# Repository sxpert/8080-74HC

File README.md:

8080 processor made of 74HC chips

original from http://userweb.alles.or.jp/chunichidenko/index.htm

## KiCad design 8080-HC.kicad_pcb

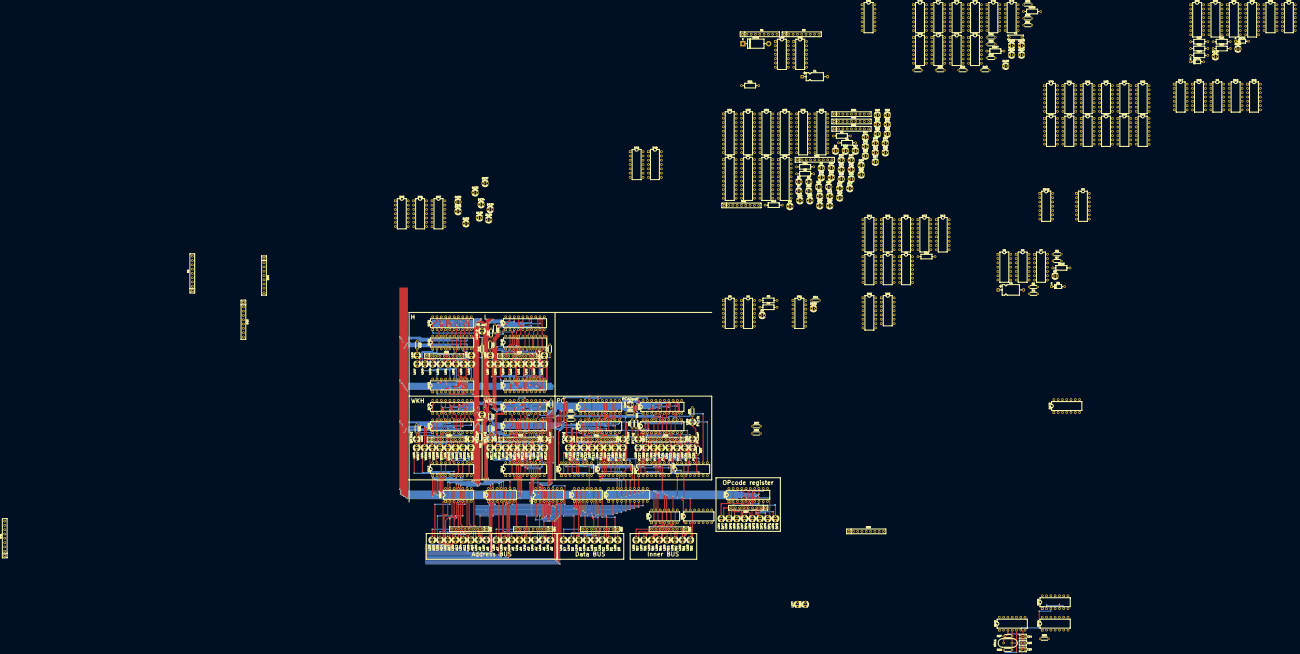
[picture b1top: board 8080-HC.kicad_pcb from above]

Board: 4 copper layers, 360 parts (0 on the bottom side), 494 nets.

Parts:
B1, B3, B5, B41, B43, B44: 1K; R_Array_SIP9
B25, B26, B29, B30, B31, B32, B33, B34, B35, B36, B37: 2.2K; R_Array_SIP9
B38: 22K; R_Array_SIP9
C1: CP; CP_Axial_L10.0mm_D4.5mm_P15.00mm_Horizontal
C2: C; C_Rect_L9.0mm_W2.5mm_P7.50mm_MKT
C4: 2.2uF; CP_Axial_L10.0mm_D6.0mm_P15.00mm_Horizontal
C14, C15: 22pF; C_Rect_L4.0mm_W2.5mm_P2.50mm
C16: 56pF; C_Rect_L4.0mm_W2.5mm_P2.50mm
D1, D2, D3, D5, D6, D7, D8, D9, D10, D11, D12, D13, D14, D15, D16, D17, D18, D19, D20, D21, D22, D23, D24, D25, D26, D27, D28, D29, D30, D31, D32, D33, D34, D35, D36, D37, D38, D39, D40, D41, D42, D43, D44, D45, D46, D47, D48, D129, D130, D132, D133, D134, D135, D136, D137, D138, D139, D140, D147, D148, D149, D150, D151, D152: LED_Small_ALT; LED_D3.0mm
D4, D141, D142: 1N4148; D_DO-35_SOD27_P7.62mm_Horizontal
D131: 1N5400; D_DO-201AD_P15.24mm_Horizontal
L145-2, L146, L155, L156, L164-2, L210, L211, L212, L213, L214, L215, L216, L217, L220, L221, L222, L223, L224, L225, L226, L227, L277, L278: LED; LED_D3.0mm
L147, L148, L149, L150, L151, L152, L153, L154, L157, L158, L159, L160, L161, L162, L163, L164, L187, L188, L189, L190, L191, L192, L193, L194, L195, L196, L197, L198, L199, L200, L201, L202, L203, L204, L205, L206, L207, L208, L209, L218, L219, L228, L229, L230, L231, L232, L233, L234, L235, L236, L237, L238, L239, L240, L241, L242, L243, L244, L245, L246, L247, L248, L249, L250, L251, L252, L253, L256, L257, L258, L259, L260, L261, L262, L263, L264, L265, L266, L267, L268, L269, L270, L271: LED_Small_ALT; LED_D3.0mm
R1, R2, R3, R8, R9, R10, R11, R12, R21, R22, R23, R24, R25, R26, R937, R938, R945: R; R_Axial_DIN0207_L6.3mm_D2.5mm_P10.16mm_Horizontal
R4, R5, R7: 10k; R_Axial_DIN0204_L3.6mm_D1.6mm_P5.08mm_Horizontal
R6: 100k; R_Axial_DIN0204_L3.6mm_D1.6mm_P5.08mm_Horizontal
R29, R37, R38, R45, R46, R47, R49, R50, R51, R52, R53, R54, R55, R56, R57, R64, R65, R66, R67, R69: 1K; R_Axial_DIN0204_L3.6mm_D1.6mm_P5.08mm_Horizontal
R32, R33, R34, R35, R36, R39, R40, R41, R42, R43, R44: R; R_Axial_DIN0204_L3.6mm_D1.6mm_P5.08mm_Horizontal
R87: 1M; R_Axial_DIN0204_L3.6mm_D1.6mm_P5.08mm_Horizontal
R88: 100; R_Axial_DIN0204_L3.6mm_D1.6mm_P5.08mm_Horizontal
R89: 10K; R_Axial_DIN0204_L3.6mm_D1.6mm_P5.08mm_Horizontal
RN1, RN2, RN3, RN4, RN5: R_Network08; R_Array_SIP9
U1, U243: 74HCU04; DIP-14_W7.62mm
U2, U19, U239: 74HC74; DIP-14_W7.62mm
U3, U5, U10, U77, U78, U81, U91, U242, U244: 74HC00; DIP-14_W7.62mm
U4, U6, U17, U43, U44, U47, U48, U49, U50, U51, U52, U57, U58, U71, U79, U93, U227, U228, U229, U230, U232, U233: 74HC04; DIP-14_W7.62mm
U7, U9, U18, U69, U90: 74HC05; DIP-14_W7.62mm
U8, U85, U89: 74HC08; DIP-14_W7.62mm
U11, U87, U88: 74HC126; DIP-14_W7.62mm
U12: 74HC161; DIP-16_W7.62mm
U13, U14, U15, U16, U53, U54, U55, U56, U92: 74HC238; DIP-16_W7.62mm
U20, U21, U22, U23, U24, U165, U166, U213, U214: 74HC373; DIP-20_W7.62mm
U25, U26, U27, U28, U29, U131, U132, U144, U145, U179, U180, U181, U182, U192, U193, U194, U195: 74HC244; DIP-20_W7.62mm
U70: 74LS05; DIP-14_W7.62mm
U72, U73, U74, U75, U76: 74LS126; DIP-14_W7.62mm
U80, U83, U84: 74HC03; DIP-14_W7.62mm
U82: 74LS11; DIP-14_W7.62mm
U86: 74LS32; DIP-14_W7.62mm
U178: 74LS03; DIP-14_W7.62mm
U215, U216, U217, U218: 74HC193; DIP-16_W7.62mm
U231: 74HC245; DIP-20_W7.62mm
U234: 74LS373; DIP-20_W7.62mm
XTAL1: 4MHz; Crystal_HC49-U_Vertical

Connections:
/BUSRQ/i_BUSRQ: R8.2, U6.5
/BUSRQ/o_BUSAK: D8.1, U6.8
/HALT/HLTA: D152.1, U49.12
/HALT/PCckdE2: U3.13, U91.3
/I/O control/OUTdE: R35.2, U72.1, U73.1, U74.1, U75.1, U76.1, U77.2, U78.1
/I/O control/Pcsel: R32.2, U58.1, U69.2
/I/O control/dataOUT: R33.2, U3.2
/I/O control/intRD: U76.2, U242.2
/I/O control/ioRD: R36.2, U72.2, U244.1
/I/O control/ioWR: R937.2, U73.2
/I/O control/memRD: R34.2, U3.1, U70.2, U71.1, U244.2
/I/O control/memWR: C2.1, R938.2, U75.2
/I/O control/o_INTRD: D151.1, U76.3
/I/O control/o_IORD: D147.1, U72.3
/I/O control/o_IOWR: D148.1, U73.3
/I/O control/o_MEMRD: D149.1, U74.3
/I/O control/o_MEMWR: D150.1, U75.3
/I/O regs/d0: B1.9, U52.3
/I/O regs/d1: B1.8, U51.1
/I/O regs/d2: B1.7, U47.13
/I/O regs/d3: B1.6, U47.11
/I/O regs/s0: B1.5, U47.9
/I/O regs/s1: B1.4, U47.5
/I/O regs/s2: B1.3, U50.3
/I/O regs/s3: B1.2, U50.1
/MOV / MVI/HLsel: U69.10, U90.2
/MOV / MVI/M2: U80.9, U80.13, U83.13, U89.4
/MOV / MVI/MCLR: U80.3, U83.8, U244.8
/MOV / MVI/MOV: U81.3, U82.10, U85.5, U86.1
/MOV / MVI/OP0: U49.9, U88.5
/MOV / MVI/OP1: U82.4, U88.2
/MOV / MVI/OP2: U82.5, U87.12
/MOV / MVI/OP3: U49.5, U87.9
/MOV / MVI/OP4: U82.2, U87.5
/MOV / MVI/OP5: U82.13, U87.2
/MOV / MVI/OP6: U71.3, U81.1
/MOV / MVI/T4: U80.4, U83.1
/MOV / MVI/T6: U80.1, U84.2, U244.10
/MOV / MVI/d!=110: U49.10, U85.9
/MOV / MVI/d=110: U49.11, U82.11, U82.12, U85.13, U89.1
/MOV / MVI/dataOUT: U69.4, U69.12
/MOV / MVI/regRD: U80.8, U90.8
/MOV / MVI/regWR: U80.6, U83.3, U84.3
/Reset/MCLR: R11.2, U2.13, U7.4, U12.1
/Reset/PCCLR: U5.3, U6.1, U6.3, U7.1, U7.3, U7.5, U7.9, U7.11
/Reset/i_RESET: R7.2, U5.1
/Reset/o_RESET: D5.1, U6.2
/Timings Generator/QE: U6.10, U13.3, U14.5, U15.5, U16.5
/regs_A_B_C_D_E/AregRD: D25.1, U25.1, U25.19
/regs_A_B_C_D_E/BregRD: D45.1, U28.1, U28.19
/regs_A_B_C_D_E/CregRD: D27.1, U26.1, U26.19
/regs_A_B_C_D_E/DregRD: D47.1, U29.1, U29.19
/regs_A_B_C_D_E/EregRD: D29.1, U27.1, U27.19
/regs_A_B_C_D_E/iB0: U20.3, U21.3, U22.3, U23.3, U24.3, U25.9, U26.9, U27.9, U28.9, U29.9
/regs_A_B_C_D_E/iB1: U20.4, U21.4, U22.4, U23.4, U24.4, U25.7, U26.7, U27.7, U28.7, U29.7
/regs_A_B_C_D_E/iB2: U20.7, U21.7, U22.7, U23.7, U24.7, U25.5, U26.5, U27.5, U28.5, U29.5
/regs_A_B_C_D_E/iB3: U20.8, U21.8, U22.8, U23.8, U24.8, U25.3, U26.3, U27.3, U28.3, U29.3
/regs_A_B_C_D_E/iB4: U20.13, U21.13, U22.13, U23.13, U24.13, U25.12, U26.12, U27.12, U28.12, U29.12
/regs_A_B_C_D_E/iB5: U20.14, U21.14, U22.14, U23.14, U24.14, U25.14, U26.14, U27.14, U28.14, U29.14
/regs_A_B_C_D_E/iB6: U20.17, U21.17, U22.17, U23.17, U24.17, U25.16, U26.16, U27.16, U28.16, U29.16
/regs_A_B_C_D_E/iB7: U20.18, U21.18, U22.18, U23.18, U24.18, U25.18, U26.18, U27.18, U28.18, U29.18
/regs_decode/HLsel: U18.2, U18.6
/regs_decode/d0: U53.1, U54.1
/regs_decode/d1: U53.2, U54.2
/regs_decode/d2: U53.3, U54.3
/regs_decode/d3: U53.6, U54.4
/regs_decode/memWR: U10.1, U19.1, U48.6
/regs_decode/regRD: D139.1, R23.2, U55.5, U56.5
/regs_decode/regWR: D140.1, R22.2, U53.5, U54.5
/regs_decode/s0: U55.1, U56.1
/regs_decode/s1: U55.2, U56.2
/regs_decode/s2: U55.3, U56.3
/regs_decode/s3: U55.6, U56.4
A0: B44.9, U132.9, U180.9, U182.18, U229.11
A1: B44.8, U132.7, U180.7, U182.16, U229.3
A2: B44.7, U132.5, U180.5, U182.14, U229.13
A3: B44.6, U132.3, U180.3, U182.12, U229.1
A4: B44.5, U132.12, U180.12, U182.3, U228.9
A5: B44.4, U132.14, U180.14, U182.5, U228.5
A6: B44.3, U132.16, U180.16, U182.7, U228.11
A7: B44.2, U132.18, U180.18, U182.9, U228.3
A8: B43.9, U131.9, U179.9, U181.18, U228.13
A9: B43.8, U131.7, U179.7, U181.16, U228.1
A10: B43.7, U131.5, U179.5, U181.14, U227.9
A11: B43.6, U131.3, U179.3, U181.12, U227.5
A12: B43.5, U131.12, U179.12, U181.3, U227.11
A13: B43.4, U131.14, U179.14, U181.5, U227.3
A14: B43.3, U131.16, U179.16, U181.7, U227.13
A15: B43.2, U131.18, U179.18, U181.9, U227.1
Exclk: R89.2, U242.5
ExclkE: L278.1, U242.13, U243.1
GND: B25.1, B26.1, B29.1, B30.1, B31.1, B32.1, B37.1, C1.2, C2.2, C4.2, C14.2, C15.2, C16.2, D131.2, R46.2, R47.2, R65.2, R66.2, RN1.1, RN2.1, RN3.1, RN4.1, RN5.1, U3.7, U5.7, U7.7, U8.7, U9.7, U10.7, U11.7, U12.3, U12.4, U12.5, U12.6, U12.8, U13.4, U13.5, U13.8, U14.4, U14.8, U15.4, U15.8, U16.8, U18.7, U19.7, U20.1, U20.10, U21.1, U21.10, U22.1, U22.10, U23.1, U23.10, U24.1, U24.10, U25.20, U26.20, U27.20, U28.20, U29.20, U43.7, U44.7, U49.7, U50.7, U51.7, U52.7, U53.4, U53.8, U54.8, U55.4, U55.8, U56.8, U69.7, U80.7, U82.7, U83.7, U84.7, U85.7, U86.7, U87.7, U88.7, U89.7, U92.8, U131.10, U132.10, U144.10, U145.10, U165.1, U165.10, U166.1, U166.10, U179.10, U180.10, U181.10, U182.10, U192.10, U193.10, U194.10, U195.10, U213.1, U213.10, U214.1, U214.10, U215.8, U216.8, U217.8, U218.8, U227.7, U228.7, U229.7, U230.7, U231.10, U232.7, U233.7, U234.1, U234.10, U239.7, U242.7, U243.7, U244.7
HLsel: L145-2.1, R29.2, U131.1, U131.19, U132.1, U132.19
HregRD: L146.1, U144.1, U144.19
HregWR: L155.2, U165.11
LregRD: L156.1, U145.1, U145.19
LregWR: L164-2.2, U166.11
unnamed: B3.2, D129.2
unnamed: B3.3, D130.2
unnamed: B3.4, D132.2
unnamed: B3.5, D134.2
unnamed: B3.6, D135.2
unnamed: B3.7, D136.2
unnamed: B3.8, D137.2
unnamed: B3.9, D138.2
unnamed: B25.2, L147.1
unnamed: B25.3, L148.1
unnamed: B25.4, L149.1
unnamed: B25.5, L150.1
unnamed: B25.6, L151.1
unnamed: B25.7, L152.1
unnamed: B25.8, L153.1
unnamed: B25.9, L154.1
unnamed: B26.2, L157.1
unnamed: B26.3, L158.1
unnamed: B26.4, L159.1
unnamed: B26.5, L160.1
unnamed: B26.6, L161.1
unnamed: B26.7, L162.1
unnamed: B26.8, L163.1
unnamed: B26.9, L164.1
unnamed: B29.2, L190.1
unnamed: B29.3, L191.1
unnamed: B29.4, L192.1
unnamed: B29.5, L193.1
unnamed: B29.6, L194.1
unnamed: B29.7, L195.1
unnamed: B29.8, L196.1
unnamed: B29.9, L197.1
unnamed: B30.2, L200.1
unnamed: B30.3, L201.1
unnamed: B30.4, L202.1
unnamed: B30.5, L203.1
unnamed: B30.6, L204.1
unnamed: B30.7, L205.1
unnamed: B30.8, L206.1
unnamed: B30.9, L207.1
unnamed: B31.2, L210.1
unnamed: B31.3, L211.1
unnamed: B31.4, L212.1
unnamed: B31.5, L213.1
unnamed: B31.6, L214.1
unnamed: B31.7, L215.1
unnamed: B31.8, L216.1
unnamed: B31.9, L217.1
unnamed: B32.2, L227.1
unnamed: B32.3, L226.1
unnamed: B32.4, L225.1
unnamed: B32.5, L224.1
unnamed: B32.6, L223.1
unnamed: B32.7, L222.1
unnamed: B32.8, L221.1
unnamed: B32.9, L220.1
unnamed: B33.2, L237.2
unnamed: B33.3, L236.2
unnamed: B33.4, L235.2
unnamed: B33.5, L234.2
unnamed: B33.6, L233.2
unnamed: B33.7, L232.2
unnamed: B33.8, L231.2
unnamed: B33.9, L230.2
unnamed: B34.2, L245.2
unnamed: B34.3, L244.2
unnamed: B34.4, L243.2
unnamed: B34.5, L242.2
unnamed: B34.6, L241.2
unnamed: B34.7, L240.2
unnamed: B34.8, L239.2
unnamed: B34.9, L238.2
unnamed: B35.2, L253.2
unnamed: B35.3, L252.2
unnamed: B35.4, L251.2
unnamed: B35.5, L250.2
unnamed: B35.6, L249.2
unnamed: B35.7, L248.2
unnamed: B35.8, L247.2
unnamed: B35.9, L246.2
unnamed: B36.2, L263.2
unnamed: B36.3, L262.2
unnamed: B36.4, L261.2
unnamed: B36.5, L260.2
unnamed: B36.6, L259.2
unnamed: B36.7, L258.2
unnamed: B36.8, L257.2
unnamed: B36.9, L256.2
unnamed: B37.2, L271.1
unnamed: B37.3, L270.1
unnamed: B37.4, L269.1
unnamed: B37.5, L268.1
unnamed: B37.6, L267.1
unnamed: B37.7, L266.1
unnamed: B37.8, L265.1
unnamed: B37.9, L264.1
unnamed: B38.6, L277.2
unnamed: B38.7, L278.2
unnamed: C4.1, D4.2, R4.2, R5.1
unnamed: C14.1, R87.2, U243.3, XTAL1.1
unnamed: C15.1, R87.1, R88.2, U243.4, XTAL1.2
unnamed: C16.1, U239.3, U243.6
unnamed: D1.1, RN1.2
unnamed: D1.2, U20.19, U25.2
unnamed: D2.1, RN2.2
unnamed: D2.2, U22.19, U26.2
unnamed: D3.1, RN3.2
unnamed: D3.2, U24.19, U27.2
unnamed: D5.2, R945.2
unnamed: D6.1, RN1.3
unnamed: D6.2, U20.16, U25.4
unnamed: D7.1, RN2.3
unnamed: D7.2, U22.16, U26.4
unnamed: D8.2, R9.2
unnamed: D9.1, RN3.3
unnamed: D9.2, U24.16, U27.4
unnamed: D10.1, RN1.4
unnamed: D10.2, U20.15, U25.6
unnamed: D11.1, RN2.4
unnamed: D11.2, U22.15, U26.6
unnamed: D12.1, RN3.4
unnamed: D12.2, U24.15, U27.6
unnamed: D13.1, RN1.5
unnamed: D13.2, U20.12, U25.8
unnamed: D14.1, RN2.5
unnamed: D14.2, U22.12, U26.8
unnamed: D15.1, RN3.5
unnamed: D15.2, U24.12, U27.8
unnamed: D16.1, RN1.6
unnamed: D16.2, U20.9, U25.17
unnamed: D17.1, RN2.6
unnamed: D17.2, U22.9, U26.17
unnamed: D18.1, RN3.6
unnamed: D18.2, U24.9, U27.17
unnamed: D19.1, RN1.7
unnamed: D19.2, U20.6, U25.15
unnamed: D20.1, RN2.7
unnamed: D20.2, U22.6, U26.15
unnamed: D21.1, RN3.7
unnamed: D21.2, U24.6, U27.15
unnamed: D22.1, RN1.8
unnamed: D22.2, U20.5, U25.13
unnamed: D23.1, RN2.8
unnamed: D23.2, U22.5, U26.13
unnamed: D24.1, RN3.8
unnamed: D24.2, U24.5, U27.13
unnamed: D25.2, R1.2
unnamed: D26.1, RN1.9
unnamed: D26.2, U20.2, U25.11
unnamed: D27.2, R2.2
unnamed: D28.1, RN2.9
unnamed: D28.2, U22.2, U26.11
unnamed: D29.2, R3.2
unnamed: D30.1, RN3.9
unnamed: D30.2, U24.2, U27.11
unnamed: D31.1, RN4.2
unnamed: D31.2, U21.19, U28.2
unnamed: D32.1, RN5.2
unnamed: D32.2, U23.19, U29.2
unnamed: D33.1, RN4.3
unnamed: D33.2, U21.16, U28.4
unnamed: D34.1, RN5.3
unnamed: D34.2, U23.16, U29.4
unnamed: D35.1, RN4.4
unnamed: D35.2, U21.15, U28.6
unnamed: D36.1, RN5.4
unnamed: D36.2, U23.15, U29.6
unnamed: D37.1, RN4.5
unnamed: D37.2, U21.12, U28.8
unnamed: D38.1, RN5.5
unnamed: D38.2, U23.12, U29.8
unnamed: D39.1, RN4.6
unnamed: D39.2, U21.9, U28.17
unnamed: D40.1, RN5.6
unnamed: D40.2, U23.9, U29.17
unnamed: D41.1, RN4.7
unnamed: D41.2, U21.6, U28.15
unnamed: D42.1, RN5.7
unnamed: D42.2, U23.6, U29.15
unnamed: D43.1, RN4.8
unnamed: D43.2, U21.5, U28.13
unnamed: D44.1, RN5.8
unnamed: D44.2, U23.5, U29.13
unnamed: D45.2, R10.2
unnamed: D46.1, RN4.9
unnamed: D46.2, U21.2, U28.11
unnamed: D47.2, R12.2
unnamed: D48.1, RN5.9
unnamed: D48.2, U23.2, U29.11
unnamed: D129.1, U50.2
unnamed: D130.1, U50.4
unnamed: D132.1, U47.6
unnamed: D133.1, U51.4
unnamed: D133.2, R21.2
unnamed: D134.1, U47.8
unnamed: D135.1, U47.10
unnamed: D136.1, U47.12
unnamed: D137.1, U51.2
unnamed: D138.1, U52.4
unnamed: D139.2, R24.2
unnamed: D140.2, R25.2
unnamed: D141.1, U52.2
unnamed: D141.2, D142.2, R26.2, U10.5
unnamed: D142.1, U19.6
unnamed: D147.2, R39.2
unnamed: D148.2, R40.2
unnamed: D149.2, R41.2
unnamed: D150.2, R42.2
unnamed: D151.2, R43.2
unnamed: D152.2, R44.2
unnamed: L145-2.2, R37.2
unnamed: L146.2, R45.2
unnamed: L147.2, U131.2, U144.2, U165.19
unnamed: L148.2, U131.4, U144.4, U165.16
unnamed: L149.2, U131.6, U144.6, U165.15
unnamed: L150.2, U131.8, U144.8, U165.12
unnamed: L151.2, U131.17, U144.17, U165.9
unnamed: L152.2, U131.15, U144.15, U165.6
unnamed: L153.2, U131.13, U144.13, U165.5
unnamed: L154.2, U131.11, U144.11, U165.2
unnamed: L155.1, R46.1
unnamed: L156.2, R38.2
unnamed: L157.2, U132.2, U145.2, U166.19
unnamed: L158.2, U132.4, U145.4, U166.16
unnamed: L159.2, U132.6, U145.6, U166.15
unnamed: L160.2, U132.8, U145.8, U166.12
unnamed: L161.2, U132.17, U145.17, U166.9
unnamed: L162.2, U132.15, U145.15, U166.6
unnamed: L163.2, U132.13, U145.13, U166.5
unnamed: L164-2.1, R47.1
unnamed: L164.2, U132.11, U145.11, U166.2
unnamed: L187.2, R49.2
unnamed: L188.2, R53.2
unnamed: L189.2, R64.2
unnamed: L190.2, U179.11, U192.11, U213.2
unnamed: L191.2, U179.13, U192.13, U213.5
unnamed: L192.2, U179.15, U192.15, U213.6
unnamed: L193.2, U179.17, U192.17, U213.9
unnamed: L194.2, U179.8, U192.8, U213.12
unnamed: L195.2, U179.6, U192.6, U213.15
unnamed: L196.2, U179.4, U192.4, U213.16
unnamed: L197.2, U179.2, U192.2, U213.19
unnamed: L198.1, R65.1
unnamed: L199.2, R50.2
unnamed: L200.2, U180.2, U193.2, U214.19
unnamed: L201.2, U180.4, U193.4, U214.16
unnamed: L202.2, U180.6, U193.6, U214.15
unnamed: L203.2, U180.8, U193.8, U214.12
unnamed: L204.2, U180.17, U193.17, U214.9
unnamed: L205.2, U180.15, U193.15, U214.6
unnamed: L206.2, U180.13, U193.13, U214.5
unnamed: L207.2, U180.11, U193.11, U214.2
unnamed: L208.1, R66.1
unnamed: L209.2, R52.2
unnamed: L210.2, U181.11, U194.11, U215.7
unnamed: L211.2, U181.13, U194.13, U215.6
unnamed: L212.2, U181.15, U194.15, U215.2
unnamed: L213.2, U181.17, U194.17, U215.3
unnamed: L214.2, U181.8, U194.8, U216.7
unnamed: L215.2, U181.6, U194.6, U216.6
unnamed: L216.2, U181.4, U194.4, U216.2
unnamed: L217.2, U181.2, U194.2, U216.3
unnamed: L218.2, R54.2
unnamed: L219.2, R55.2
unnamed: L220.2, U182.11, U195.11, U217.7
unnamed: L221.2, U182.13, U195.13, U217.6
unnamed: L222.2, U182.15, U195.15, U217.2
unnamed: L223.2, U182.17, U195.17, U217.3
unnamed: L224.2, U182.8, U195.8, U218.7
unnamed: L225.2, U182.6, U195.6, U218.6
unnamed: L226.2, U182.4, U195.4, U218.2
unnamed: L227.2, U182.2, U195.2, U218.3
unnamed: L228.2, R67.2
unnamed: L229.2, R56.2
unnamed: L230.1, U227.2
unnamed: L231.1, U227.12
unnamed: L232.1, U227.4
unnamed: L233.1, U227.10
unnamed: L234.1, U227.6
unnamed: L235.1, U227.8
unnamed: L236.1, U228.2
unnamed: L237.1, U228.12
unnamed: L238.1, U228.4
unnamed: L239.1, U228.10
unnamed: L240.1, U228.6
unnamed: L241.1, U228.8
unnamed: L242.1, U229.2
unnamed: L243.1, U229.12
unnamed: L244.1, U229.4
unnamed: L245.1, U229.10
unnamed: L246.1, U229.6
unnamed: L247.1, U229.8
unnamed: L248.1, U230.2
unnamed: L249.1, U230.12
unnamed: L250.1, U230.4
unnamed: L251.1, U230.10
unnamed: L252.1, U230.6
unnamed: L253.1, U230.8
unnamed: L256.1, U232.2
unnamed: L257.1, U232.12
unnamed: L258.1, U232.4
unnamed: L259.1, U232.10
unnamed: L260.1, U232.6
unnamed: L261.1, U232.8
unnamed: L262.1, U233.2
unnamed: L263.1, U233.12
unnamed: R5.2, R6.1, U1.9
unnamed: R6.2, U1.10, U5.2
unnamed: R88.1, U243.5
unnamed: U1.8, U1.11
unnamed: U2.8, U2.12, U6.11
unnamed: U3.3, U77.1
unnamed: U3.11, U49.13, U88.9, U91.1
unnamed: U3.8, U3.12
unnamed: U6.6, U8.2
unnamed: U6.9, U8.3, U9.1, U9.3
unnamed: U10.2, U10.6
unnamed: U10.3, U10.4, U18.1, U18.3, U19.2
unnamed: U11.2, U12.14, U15.1, U16.1
unnamed: U11.5, U12.13, U14.1, U15.2, U16.2
unnamed: U11.9, U12.11, U13.2, U14.3, U15.6, U16.4
unnamed: U11.12, U12.12, U13.1, U14.2, U15.3, U16.3
unnamed: U2.11, U12.15
unnamed: U18.5, U18.9, U57.4
unnamed: U19.3, U58.4
unnamed: U48.5, U53.9
unnamed: U48.9, U54.13
unnamed: U48.11, U54.12
unnamed: U48.13, U54.11
unnamed: U49.6, U82.1
unnamed: U49.8, U82.3
unnamed: U54.10, U57.1
unnamed: U55.9, U57.3
unnamed: U58.2, U70.1, U78.2
unnamed: U69.3, U89.6, U90.1
unnamed: U69.9, U83.9, U83.12, U84.1, U84.4, U85.11
unnamed: U69.11, U69.13, U84.6, U90.9
unnamed: U80.2, U80.5, U80.10, U85.6, U89.2
unnamed: U80.12, U83.2, U83.4, U85.3, U85.10, U85.12, U86.2
unnamed: U82.6, U82.9, U85.2
unnamed: U84.12, U88.8
unnamed: U86.3, U87.1, U87.4, U87.10, U87.13, U88.1, U88.4
unnamed: U89.3, U89.5
unnamed: U89.9, U92.14
unnamed: U89.10, U93.2
unnamed: U215.5, U216.13
unnamed: U216.5, U217.13
unnamed: U217.5, U218.13
unnamed: U239.1, U239.4
unnamed: U239.2, U239.6
unnamed: U239.5, U242.12
unnamed: U71.2, U242.1
unnamed: U74.2, U242.3
unnamed: U242.4, U243.2
unnamed: U242.6, U242.9, U244.12
unnamed: U242.10, U242.11, U244.13
unnamed: U79.2, U81.2, U244.4
unnamed: U71.4, U244.5
unnamed: U85.1, U244.6
unnamed: U85.8, U244.9
OP0: L271.2, U234.2
OP1: L270.2, U234.5
OP2: L269.2, U234.6
OP3: L268.2, U234.9
OP4: L267.2, U234.12
OP5: L266.2, U234.15
OP6: L265.2, U234.16
OP7: L264.2, U234.19
PCADout: L188.1, U181.1, U181.19, U182.1, U182.19
PCCLR: U215.14, U216.14, U217.14, U218.14
PCHregRD: L209.1, U194.1, U194.19
PCHregWR: U215.11, U216.11
PCLregRD: L219.1, U195.1, U195.19
PCLregWR: L228.1, U217.11, U218.11
PCclk: L229.1, R57.2, R69.2, U178.6, U218.5
VCC: B1.1, B3.1, B5.1, B33.1, B34.1, B35.1, B36.1, B38.1, B41.1, B43.1, B44.1, C1.1, D4.1, D131.1, R1.1, R2.1, R3.1, R4.1, R7.1, R8.1, R9.1, R10.1, R11.1, R12.1, R21.1, R22.1, R23.1, R24.1, R25.1, R26.1, R29.1, R32.1, R33.1, R34.1, R35.1, R36.1, R37.1, R38.1, R39.1, R40.1, R41.1, R42.1, R43.1, R44.1, R45.1, R49.1, R50.1, R51.2, R52.1, R53.1, R54.1, R55.1, R56.1, R57.1, R64.1, R67.1, R69.1, R89.1, R937.1, R938.1, R945.1, U2.10, U3.14, U5.14, U7.14, U8.14, U9.14, U10.14, U11.4, U11.10, U11.13, U11.14, U12.7, U12.9, U12.10, U12.16, U13.6, U13.16, U14.6, U14.16, U15.16, U16.6, U16.16, U18.14, U19.4, U19.14, U20.20, U21.20, U22.20, U23.20, U24.20, U25.10, U26.10, U27.10, U28.10, U29.10, U43.14, U44.14, U49.14, U50.14, U51.3, U51.14, U52.14, U53.16, U54.6, U54.16, U55.16, U56.6, U56.16, U69.14, U80.14, U82.14, U83.14, U84.14, U85.14, U86.14, U87.14, U88.10, U88.14, U89.14, U92.6, U92.16, U131.20, U132.20, U144.20, U145.20, U165.20, U166.20, U179.20, U180.20, U181.20, U182.20, U192.20, U193.20, U194.20, U195.20, U213.20, U214.20, U215.4, U215.16, U216.4, U216.16, U217.4, U217.16, U218.4, U218.16, U227.14, U228.14, U229.14, U230.14, U231.20, U232.14, U233.14, U234.20, U239.14, U242.14, U243.14, U244.14
WKHregRD: L189.1, U192.1, U192.19
WKHregWR: L198.2, U213.11
WKLregRD: L199.1, U193.1, U193.19
WKLregWR: L208.2, U214.11
WKsel: L187.1, R51.1, U179.1, U179.19, U180.1, U180.19
iB0: B5.2, U144.9, U145.9, U165.3, U166.3, U192.9, U193.9, U194.18, U195.18, U213.3, U214.3, U216.15, U218.15, U231.18, U233.13, U234.3
iB1: B5.3, U144.7, U145.7, U165.4, U166.4, U192.7, U193.7, U194.16, U195.16, U213.4, U214.4, U216.1, U218.1, U231.17, U233.1, U234.4
iB2: B5.4, U144.5, U145.5, U165.7, U166.7, U192.5, U193.5, U194.14, U195.14, U213.7, U214.7, U216.10, U218.10, U231.16, U232.9, U234.7
iB3: B5.5, U144.3, U145.3, U165.8, U166.8, U192.3, U193.3, U194.12, U195.12, U213.8, U214.8, U216.9, U218.9, U231.15, U232.5, U234.8
iB4: B5.6, U144.12, U145.12, U165.13, U166.13, U192.12, U193.12, U194.3, U195.3, U213.13, U214.13, U215.15, U217.15, U231.14, U232.11, U234.13
iB5: B5.7, U144.14, U145.14, U165.14, U166.14, U192.14, U193.14, U194.5, U195.5, U213.14, U214.14, U215.1, U217.1, U231.13, U232.3, U234.14
iB6: B5.8, U144.16, U145.16, U165.17, U166.17, U192.16, U193.16, U194.7, U195.7, U213.17, U214.17, U215.10, U217.10, U231.12, U232.13, U234.17
iB7: B5.9, U144.18, U145.18, U165.18, U166.18, U192.18, U193.18, U194.9, U195.9, U213.18, U214.18, U215.9, U217.9, U231.11, U232.1, U234.18
io_D0: B41.2, U230.9, U231.2
io_D1: B41.3, U230.5, U231.3
io_D2: B41.4, U230.11, U231.4
io_D3: B41.5, U230.3, U231.5
io_D4: B41.6, U230.13, U231.6
io_D5: B41.7, U230.1, U231.7
io_D6: B41.8, U229.9, U231.8
io_D7: B41.9, U229.5, U231.9

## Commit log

2019-03-26 add files
2019-03-26 finish routing the PC module
2019-03-26 start routing the OPcode register, we have a piece of the iBn bus
2019-03-26 OPcode register block completely routed
2019-03-26 place leds and inverters for the iBn bus
2019-03-27 iBn bus inverters and leds completely routed
2019-03-27 cleanup .gitignore
2019-03-27 finished Inner BUS, added screenshot
2019-03-27 nothing significant
2019-03-27 place u229, u230 and D0-D7 leds
2019-03-27 address display leds set and half routed
2019-03-27 address display all routed
2019-03-27 placed WKL register, start routing
2019-03-27 all WKL leds routed
2019-03-27 move a couple of components to cleanup ratsnets
2019-03-27 route A0-A3
2019-03-27 oops, had to redo part of the PC because I inverted U182 and U195, also routed A0-A7 through the PC register
2019-03-27 fix a couple missing traces
2019-03-28 route part of A8-A15 from WKL to WKH
2019-03-28 finish routing A8-A15 from WKL to WKH
2019-03-28 finish routing A8-A15 around WKH
2019-03-28 almost finished routing WKH
2019-03-28 optimize iB0-iB7 bus under U231
2019-03-28 optimize iB0-iB7 under U234
2019-03-28 WKH all done
2019-03-28 annotate HL registers
2019-03-28 route the iBn bus on the left side of the board
2019-03-28 start routing iBn through H/L. I may have to redo things for WKH/WKL and PC at a later time
2019-03-28 U165 has iBn entierely routed
2019-03-28 propagate iBn all along the U165 / U166 ... line
2019-03-29 optimized under U165, start routing under U166
2019-03-29 route A8-A15 to U131
2019-03-29 start routing A0-A1 to U132
2019-03-29 more routing of A0-A7
2019-03-30 more routing of A0-A7 towards U132
2019-03-30 start re-working A8-A15
2019-03-30 finally done with A0-A15 for HL registers
2019-03-30 route things in the L register
2019-03-30 L register entirely routed
2019-03-30 partially optimize WKL
2019-03-30 optimize ground plane around B30
2019-04-01 more updates to HL
2019-04-01 rework WKH entirely
2019-04-01 optimize WKL
2019-04-01 optimize PC
2019-04-01 done with HL
